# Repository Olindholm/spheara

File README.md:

# Spheara

Follow the progress of the project on my blog at lindholm.tk, or just straight into one of the chapers:

1. [Project Description](https://lindholm.tk/post/2)
1. [Control Loop Specification](https://lindholm.tk/post/3)
1. [Sourcing Parts](https://lindholm.tk/post/4)
1. [Making a LED blink](https://lindholm.tk/post/5)
1. [Designing the PCB](https://lindholm.tk/post/6)
1. [Testing the PCB](https://lindholm.tk/post/7)

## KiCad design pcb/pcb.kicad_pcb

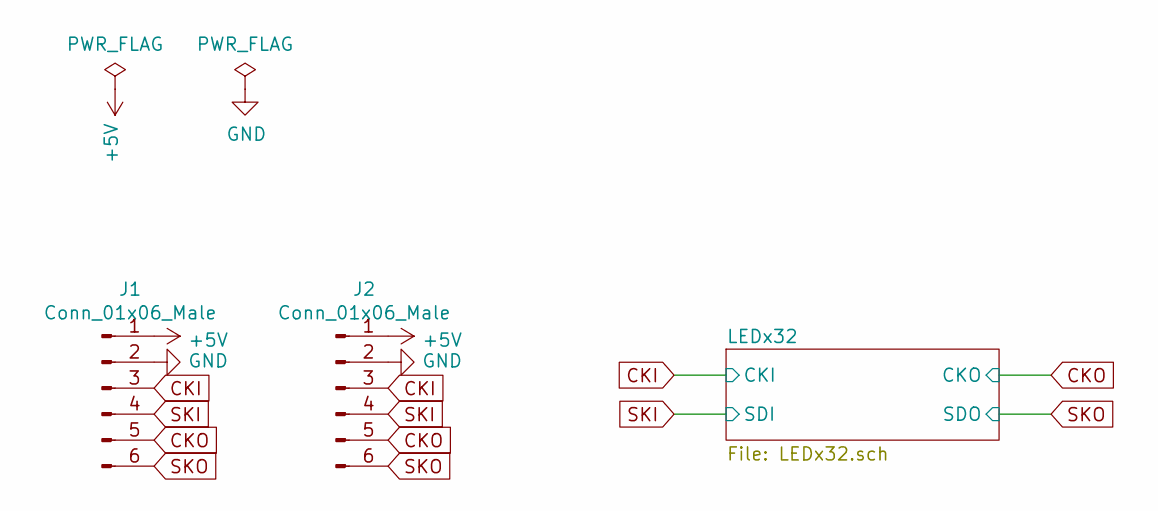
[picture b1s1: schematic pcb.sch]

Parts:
J1, J2: Conn_01x06_Male; JST_XH_B6B-XH-A_1x06_P2.50mm_Vertical

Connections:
+5V: J1.1, J2.1; also elsewhere on the board
CKI: J1.3, J2.3; also elsewhere on the board
CKO: J1.5, J2.5; also elsewhere on the board
GND: J1.2, J2.2; also elsewhere on the board
SKI: J1.4, J2.4; also elsewhere on the board
SKO: J1.6, J2.6; also elsewhere on the board

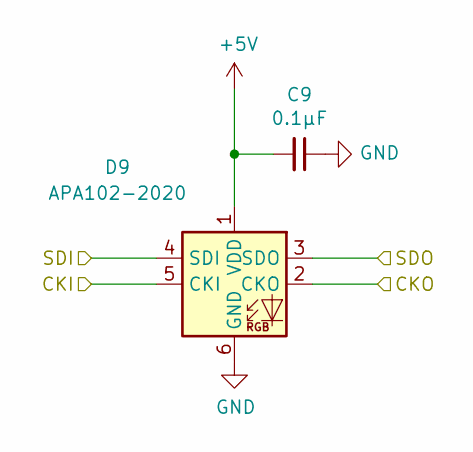
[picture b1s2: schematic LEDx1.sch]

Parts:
C5: 0.1μF; C_0603_1608Metric
D5: APA102-2020; LED-APA102-2020

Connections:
+5V: C5.2, D5.1 (VDD); also elsewhere on the board
/LEDx32/LEDx16A/LEDx8A/LEDx4B/CKI: D5.5 (CKI); also elsewhere on the board
/LEDx32/LEDx16A/LEDx8A/LEDx4B/LEDx2A/LEDx1B/CKI: D5.2 (CKO); also elsewhere on the board
/LEDx32/LEDx16A/LEDx8A/LEDx4B/LEDx2A/LEDx1B/SDI: D5.3 (SDO); also elsewhere on the board
/LEDx32/LEDx16A/LEDx8A/LEDx4B/SDI: D5.4 (SDI); also elsewhere on the board
GND: C5.1, D5.6 (GND); also elsewhere on the board

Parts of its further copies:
C1, C2, C3, C4, C6, C7, C8, C9, C10, C11, C12, C13, C14, C15, C16, C17, C18, C19, C20, C21, C22, C23, C24, C25, C26, C27, C28, C29, C30, C31, C32: 0.1μF; C_0603_1608Metric
D1, D2, D3, D4, D6, D7, D8, D9, D10, D11, D12, D13, D14, D15, D16, D17, D18, D19, D20, D21, D22, D23, D24, D25, D26, D27, D28, D29, D30, D31, D32: APA102-2020; LED-APA102-2020

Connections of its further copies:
+5V: C1.2, C2.2, C3.2, C4.2, C6.2, C7.2, C8.2, C9.2, C10.2, C11.2, C12.2, C13.2, C14.2, C15.2, C16.2, C17.2, C18.2, C19.2, C20.2, C21.2, C22.2, C23.2, C24.2, C25.2, C26.2, C27.2, C28.2, C29.2, C30.2, C31.2, C32.2, D1.1 (VDD), D2.1 (VDD), D3.1 (VDD), D4.1 (VDD), D6.1 (VDD), D7.1 (VDD), D8.1 (VDD), D9.1 (VDD), D10.1 (VDD), D11.1 (VDD), D12.1 (VDD), D13.1 (VDD), D14.1 (VDD), D15.1 (VDD), D16.1 (VDD), D17.1 (VDD), D18.1 (VDD), D19.1 (VDD), D20.1 (VDD), D21.1 (VDD), D22.1 (VDD), D23.1 (VDD), D24.1 (VDD), D25.1 (VDD), D26.1 (VDD), D27.1 (VDD), D28.1 (VDD), D29.1 (VDD), D30.1 (VDD), D31.1 (VDD), D32.1 (VDD); also elsewhere on the board
/LEDx32/LEDx16A/LEDx8A/LEDx4A/LEDx2A/LEDx1B/CKI: D1.2 (CKO), D2.5 (CKI)
/LEDx32/LEDx16A/LEDx8A/LEDx4A/LEDx2A/LEDx1B/SDI: D1.3 (SDO), D2.4 (SDI)
/LEDx32/LEDx16A/LEDx8A/LEDx4A/LEDx2B/CKI: D2.2 (CKO), D3.5 (CKI)
/LEDx32/LEDx16A/LEDx8A/LEDx4A/LEDx2B/LEDx1B/CKI: D3.2 (CKO), D4.5 (CKI)
/LEDx32/LEDx16A/LEDx8A/LEDx4A/LEDx2B/LEDx1B/SDI: D3.3 (SDO), D4.4 (SDI)
/LEDx32/LEDx16A/LEDx8A/LEDx4A/LEDx2B/SDI: D2.3 (SDO), D3.4 (SDI)
/LEDx32/LEDx16A/LEDx8A/LEDx4B/CKI: D4.2 (CKO); also elsewhere on the board
/LEDx32/LEDx16A/LEDx8A/LEDx4B/LEDx2A/LEDx1B/CKI: D6.5 (CKI); also elsewhere on the board
/LEDx32/LEDx16A/LEDx8A/LEDx4B/LEDx2A/LEDx1B/SDI: D6.4 (SDI); also elsewhere on the board
/LEDx32/LEDx16A/LEDx8A/LEDx4B/LEDx2B/CKI: D6.2 (CKO), D7.5 (CKI)
/LEDx32/LEDx16A/LEDx8A/LEDx4B/LEDx2B/LEDx1B/CKI: D7.2 (CKO), D8.5 (CKI)
/LEDx32/LEDx16A/LEDx8A/LEDx4B/LEDx2B/LEDx1B/SDI: D7.3 (SDO), D8.4 (SDI)
/LEDx32/LEDx16A/LEDx8A/LEDx4B/LEDx2B/SDI: D6.3 (SDO), D7.4 (SDI)
/LEDx32/LEDx16A/LEDx8A/LEDx4B/SDI: D4.3 (SDO); also elsewhere on the board
/LEDx32/LEDx16A/LEDx8B/CKI: D8.2 (CKO), D9.5 (CKI)
/LEDx32/LEDx16A/LEDx8B/LEDx4A/LEDx2A/LEDx1B/CKI: D9.2 (CKO), D10.5 (CKI)
/LEDx32/LEDx16A/LEDx8B/LEDx4A/LEDx2A/LEDx1B/SDI: D9.3 (SDO), D10.4 (SDI)
/LEDx32/LEDx16A/LEDx8B/LEDx4A/LEDx2B/CKI: D10.2 (CKO), D11.5 (CKI)
/LEDx32/LEDx16A/LEDx8B/LEDx4A/LEDx2B/LEDx1B/CKI: D11.2 (CKO), D12.5 (CKI)
/LEDx32/LEDx16A/LEDx8B/LEDx4A/LEDx2B/LEDx1B/SDI: D11.3 (SDO), D12.4 (SDI)
/LEDx32/LEDx16A/LEDx8B/LEDx4A/LEDx2B/SDI: D10.3 (SDO), D11.4 (SDI)
/LEDx32/LEDx16A/LEDx8B/LEDx4B/CKI: D12.2 (CKO), D13.5 (CKI)
/LEDx32/LEDx16A/LEDx8B/LEDx4B/LEDx2A/LEDx1B/CKI: D13.2 (CKO), D14.5 (CKI)
/LEDx32/LEDx16A/LEDx8B/LEDx4B/LEDx2A/LEDx1B/SDI: D13.3 (SDO), D14.4 (SDI)
/LEDx32/LEDx16A/LEDx8B/LEDx4B/LEDx2B/CKI: D14.2 (CKO), D15.5 (CKI)
/LEDx32/LEDx16A/LEDx8B/LEDx4B/LEDx2B/LEDx1B/CKI: D15.2 (CKO), D16.5 (CKI)
/LEDx32/LEDx16A/LEDx8B/LEDx4B/LEDx2B/LEDx1B/SDI: D15.3 (SDO), D16.4 (SDI)
/LEDx32/LEDx16A/LEDx8B/LEDx4B/LEDx2B/SDI: D14.3 (SDO), D15.4 (SDI)
/LEDx32/LEDx16A/LEDx8B/LEDx4B/SDI: D12.3 (SDO), D13.4 (SDI)
/LEDx32/LEDx16A/LEDx8B/SDI: D8.3 (SDO), D9.4 (SDI)
/LEDx32/LEDx16B/CKI: D16.2 (CKO), D17.5 (CKI)
/LEDx32/LEDx16B/LEDx8A/LEDx4A/LEDx2A/LEDx1B/CKI: D17.2 (CKO), D18.5 (CKI)
/LEDx32/LEDx16B/LEDx8A/LEDx4A/LEDx2A/LEDx1B/SDI: D17.3 (SDO), D18.4 (SDI)
/LEDx32/LEDx16B/LEDx8A/LEDx4A/LEDx2B/CKI: D18.2 (CKO), D19.5 (CKI)
/LEDx32/LEDx16B/LEDx8A/LEDx4A/LEDx2B/LEDx1B/CKI: D19.2 (CKO), D20.5 (CKI)
/LEDx32/LEDx16B/LEDx8A/LEDx4A/LEDx2B/LEDx1B/SDI: D19.3 (SDO), D20.4 (SDI)
/LEDx32/LEDx16B/LEDx8A/LEDx4A/LEDx2B/SDI: D18.3 (SDO), D19.4 (SDI)
/LEDx32/LEDx16B/LEDx8A/LEDx4B/CKI: D20.2 (CKO), D21.5 (CKI)
/LEDx32/LEDx16B/LEDx8A/LEDx4B/LEDx2A/LEDx1B/CKI: D21.2 (CKO), D22.5 (CKI)
/LEDx32/LEDx16B/LEDx8A/LEDx4B/LEDx2A/LEDx1B/SDI: D21.3 (SDO), D22.4 (SDI)
/LEDx32/LEDx16B/LEDx8A/LEDx4B/LEDx2B/CKI: D22.2 (CKO), D23.5 (CKI)
/LEDx32/LEDx16B/LEDx8A/LEDx4B/LEDx2B/LEDx1B/CKI: D23.2 (CKO), D24.5 (CKI)
/LEDx32/LEDx16B/LEDx8A/LEDx4B/LEDx2B/LEDx1B/SDI: D23.3 (SDO), D24.4 (SDI)
/LEDx32/LEDx16B/LEDx8A/LEDx4B/LEDx2B/SDI: D22.3 (SDO), D23.4 (SDI)
/LEDx32/LEDx16B/LEDx8A/LEDx4B/SDI: D20.3 (SDO), D21.4 (SDI)
/LEDx32/LEDx16B/LEDx8B/CKI: D24.2 (CKO), D25.5 (CKI)
/LEDx32/LEDx16B/LEDx8B/LEDx4A/LEDx2A/LEDx1B/CKI: D25.2 (CKO), D26.5 (CKI)
/LEDx32/LEDx16B/LEDx8B/LEDx4A/LEDx2A/LEDx1B/SDI: D25.3 (SDO), D26.4 (SDI)
/LEDx32/LEDx16B/LEDx8B/LEDx4A/LEDx2B/CKI: D26.2 (CKO), D27.5 (CKI)
/LEDx32/LEDx16B/LEDx8B/LEDx4A/LEDx2B/LEDx1B/CKI: D27.2 (CKO), D28.5 (CKI)
/LEDx32/LEDx16B/LEDx8B/LEDx4A/LEDx2B/LEDx1B/SDI: D27.3 (SDO), D28.4 (SDI)
/LEDx32/LEDx16B/LEDx8B/LEDx4A/LEDx2B/SDI: D26.3 (SDO), D27.4 (SDI)
/LEDx32/LEDx16B/LEDx8B/LEDx4B/CKI: D28.2 (CKO), D29.5 (CKI)
/LEDx32/LEDx16B/LEDx8B/LEDx4B/LEDx2A/LEDx1B/CKI: D29.2 (CKO), D30.5 (CKI)
/LEDx32/LEDx16B/LEDx8B/LEDx4B/LEDx2A/LEDx1B/SDI: D29.3 (SDO), D30.4 (SDI)
/LEDx32/LEDx16B/LEDx8B/LEDx4B/LEDx2B/CKI: D30.2 (CKO), D31.5 (CKI)
/LEDx32/LEDx16B/LEDx8B/LEDx4B/LEDx2B/LEDx1B/CKI: D31.2 (CKO), D32.5 (CKI)
/LEDx32/LEDx16B/LEDx8B/LEDx4B/LEDx2B/LEDx1B/SDI: D31.3 (SDO), D32.4 (SDI)
/LEDx32/LEDx16B/LEDx8B/LEDx4B/LEDx2B/SDI: D30.3 (SDO), D31.4 (SDI)
/LEDx32/LEDx16B/LEDx8B/LEDx4B/SDI: D28.3 (SDO), D29.4 (SDI)
/LEDx32/LEDx16B/LEDx8B/SDI: D24.3 (SDO), D25.4 (SDI)
/LEDx32/LEDx16B/SDI: D16.3 (SDO), D17.4 (SDI)
CKI: D1.5 (CKI); also elsewhere on the board
CKO: D32.2 (CKO); also elsewhere on the board
GND: C1.1, C2.1, C3.1, C4.1, C6.1, C7.1, C8.1, C9.1, C10.1, C11.1, C12.1, C13.1, C14.1, C15.1, C16.1, C17.1, C18.1, C19.1, C20.1, C21.1, C22.1, C23.1, C24.1, C25.1, C26.1, C27.1, C28.1, C29.1, C30.1, C31.1, C32.1, D1.6 (GND), D2.6 (GND), D3.6 (GND), D4.6 (GND), D6.6 (GND), D7.6 (GND), D8.6 (GND), D9.6 (GND), D10.6 (GND), D11.6 (GND), D12.6 (GND), D13.6 (GND), D14.6 (GND), D15.6 (GND), D16.6 (GND), D17.6 (GND), D18.6 (GND), D19.6 (GND), D20.6 (GND), D21.6 (GND), D22.6 (GND), D23.6 (GND), D24.6 (GND), D25.6 (GND), D26.6 (GND), D27.6 (GND), D28.6 (GND), D29.6 (GND), D30.6 (GND), D31.6 (GND), D32.6 (GND); also elsewhere on the board
SKI: D1.4 (SDI); also elsewhere on the board
SKO: D32.3 (SDO); also elsewhere on the board

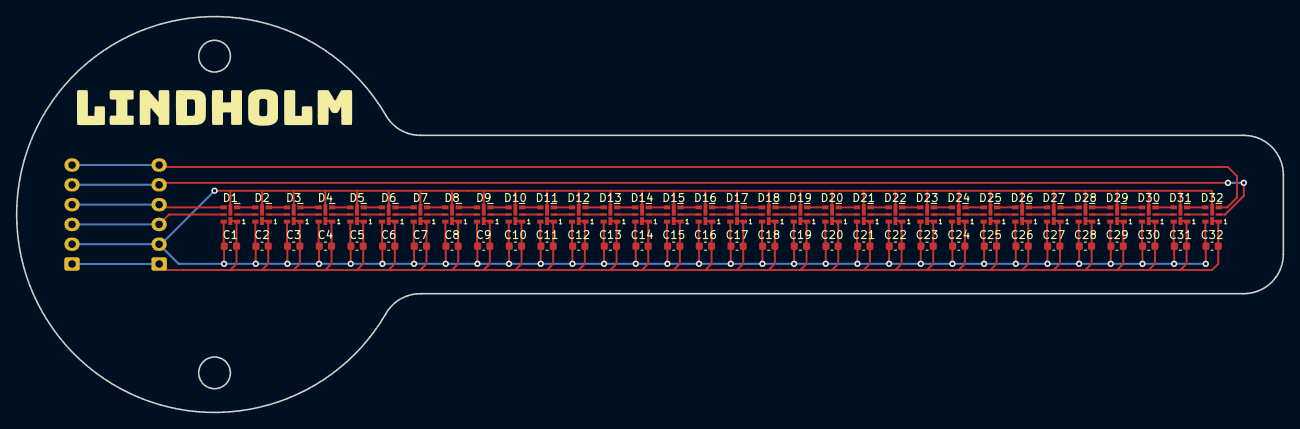
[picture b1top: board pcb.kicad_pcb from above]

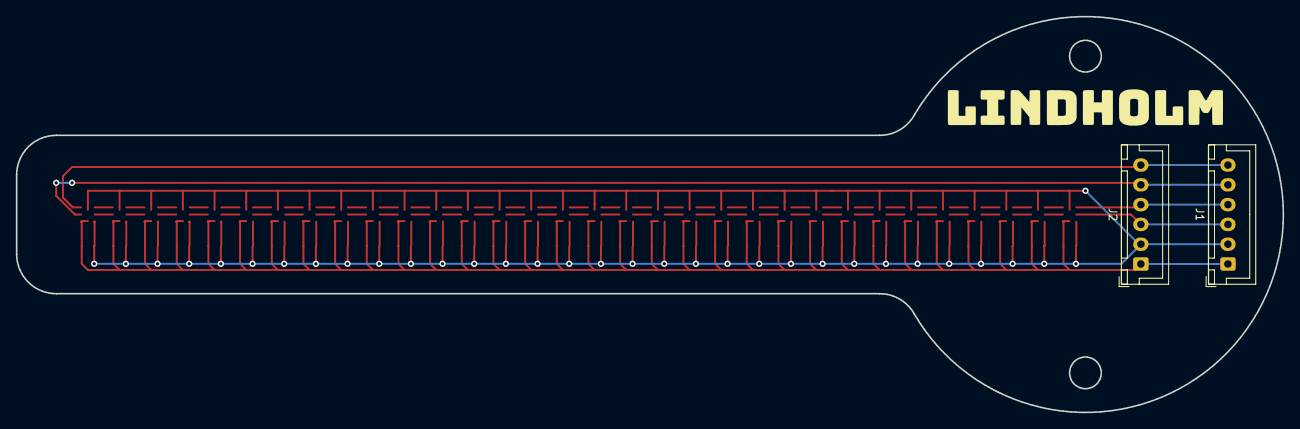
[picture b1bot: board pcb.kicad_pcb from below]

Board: 2 copper layers, 160.0 x 50.0 mm, 66 parts (2 on the bottom side), 68 nets.

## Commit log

2021-06-16 Add missing assets
2021-09-12 Reference blog in readme
2021-09-18 Initial firmware (LED blink)
2021-09-18 Create PCB design
2021-09-19 Make a LED blink!
2021-09-19 Specify tab standard for vscode
2021-09-19 Update README with new post
2021-09-19 Make more LEDs blink
